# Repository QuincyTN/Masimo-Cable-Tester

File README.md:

# Masimo-Cable-Tester
This repository describes SD Cables sponsored project: “Automated multi conductor
cable break-short detector,” hereinafter referred to as the “Cable Tester.” The Cable Tester
continuously monitors a multi-conductor cable that is being subjected to destructive mechanical
testing, measuring resistance and detecting any breaks or shorts. The team is developing a
Printed Circuit Board (PCB) that will have serval inputs and outputs (I/O), including SD card
port, 20-pin connector, power switch, DC power jack, a debugger, banana jack, and a Human
Machine Interface (HMI). For the HMI, the team will be using a Liquid Crystal Display (LCD)
to display the Graphic User Interface (GUI), which is shown for use case. We will be using the
AVR128DB64 microcontroller (MCU) help to drive our device.

The Cable Tester is a device that must test and analyze the
durability and integrity of wires. The device must extract data from the wire connected to
characterize it and monitor the changes in the wire that may indicate ashort or a break in the
conductors while the wire is subjected to a destructive mechanical test, such as a bend cycle test.
All data must be captured in an SD card inserted into the device for post-test analysis. Currently,
the Cable Tester that Masimo possesses operates with preset assumptions about the wire it will
attach. The Cable Tester that we design must be universal to all wires, more specifically, it must
characterize the cable regardless of what wire is connected and then proceed with the tests. The
universalizability of the Cable Tester will assist Masimo, and potentially other companies, in the
development of electrical systems by predetermining faults in the wires before it will be
implemented into the system, which prevents future technical issues.

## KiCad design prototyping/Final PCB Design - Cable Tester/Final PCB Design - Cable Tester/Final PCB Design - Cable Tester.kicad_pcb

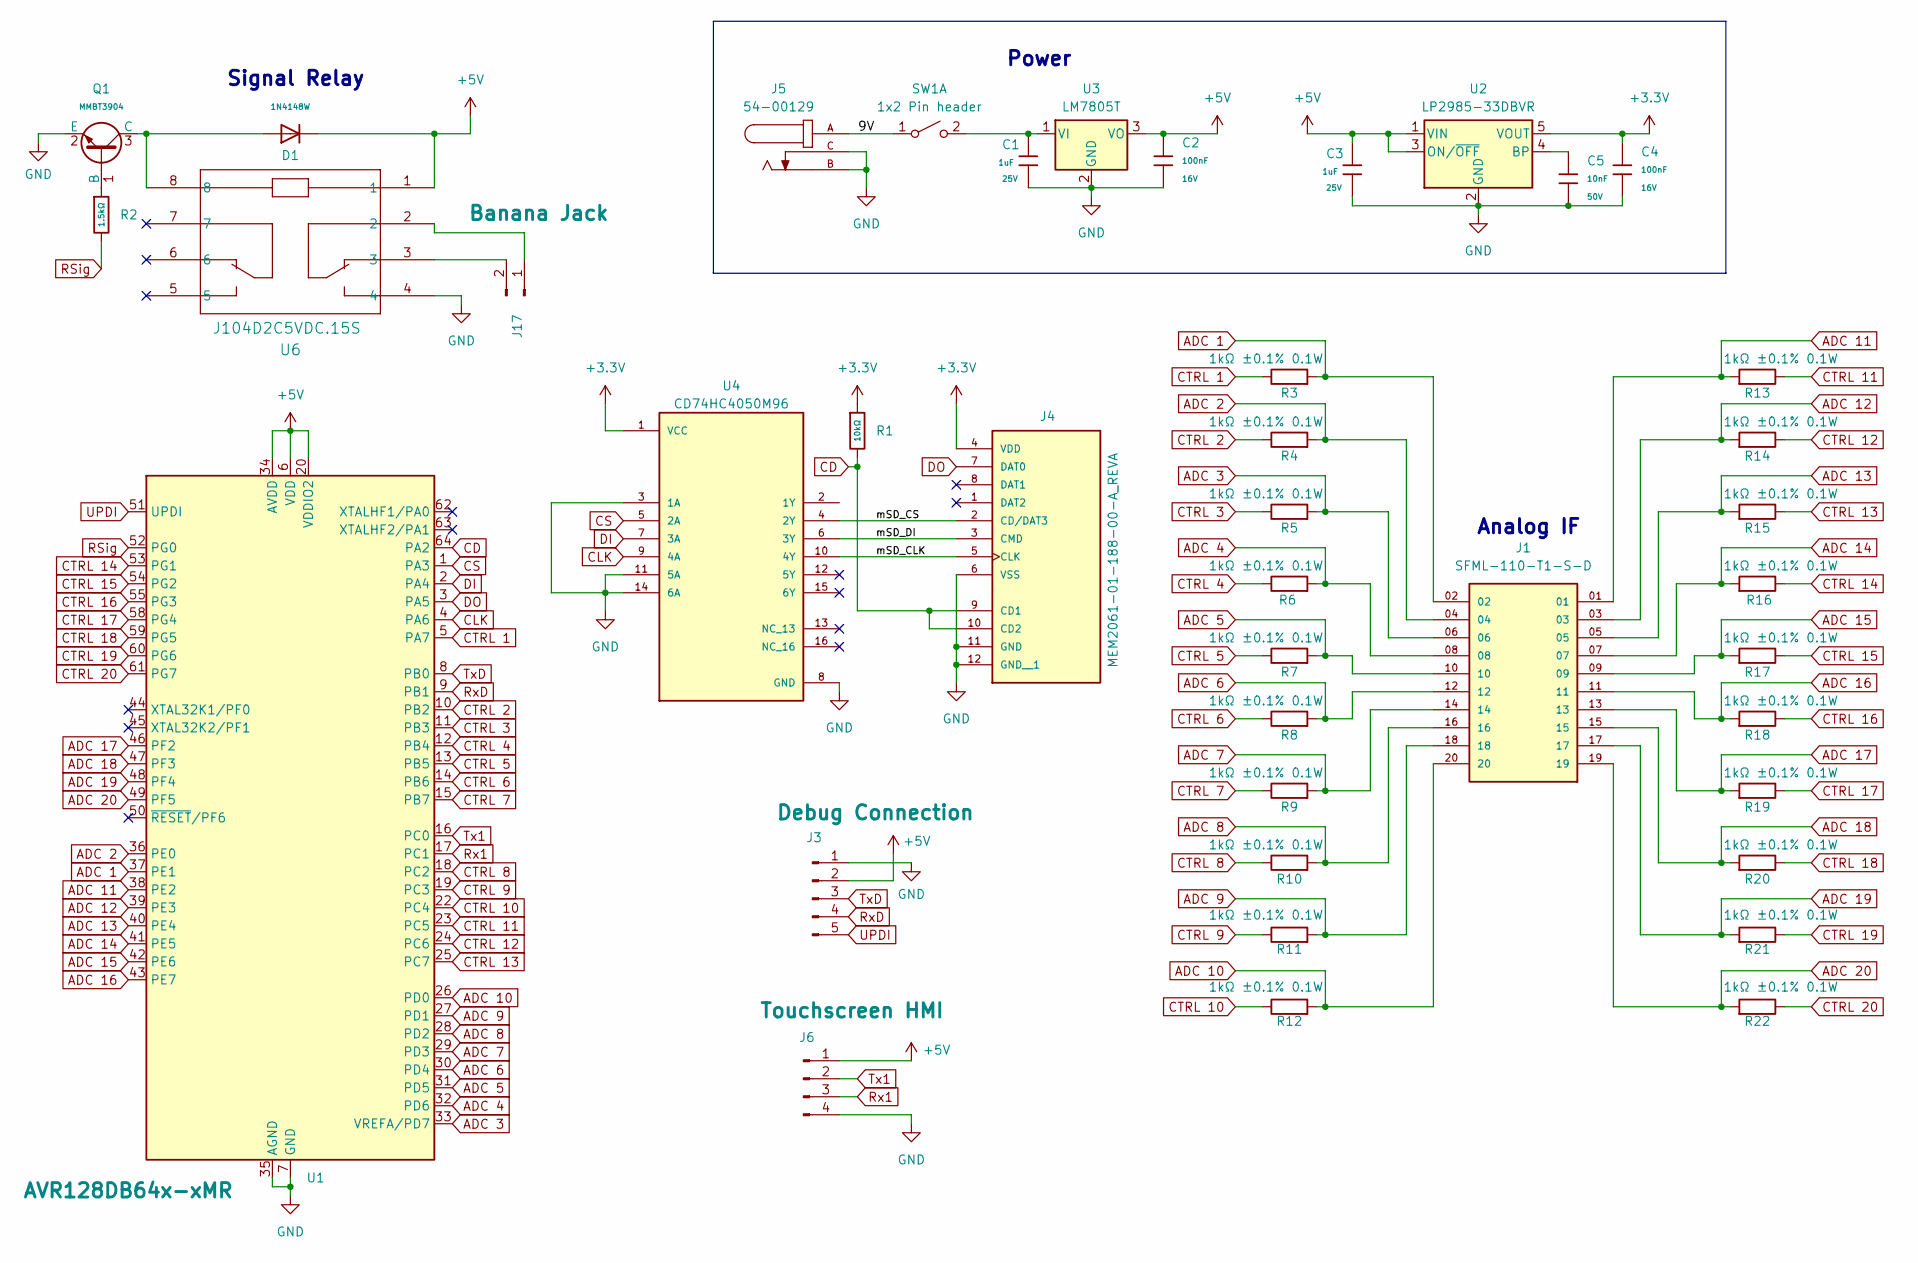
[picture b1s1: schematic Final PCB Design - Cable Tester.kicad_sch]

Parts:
C1, C3: 1uF; C_0402; Voltage Rated 25V; Tolerance ±10%; Part CL05A105KA5NQNC; LCSC C52923
C2, C4: 100nF; C_0402; Voltage Rated 16V; Tolerance ±10%; Part CL05B104KO5NNNC; LCSC C1525
C5: 10nF; C_0402; Voltage Rated 50V; Tolerance ±10%; Part CL05B103KB5NNNC; LCSC C15195
D1: 1N4148W; D_SOD-123; Forward Voltage (Vf@If) 1V@50mA; Reverse Voltage (Vr) 75V; Part 1N4148W; LCSC C81598
J1: SFML-110-T1-S-D; SAMTEC_SFML-110-T1-S-D; PARTREV E
J3: Debug Connection; PinHeader_1x05_P2.54mm_Vertical
J4: MEM2061-01-188-00-A_REVA; GCT_MEM2061-01-188-00-A_REVA
J5: 54-00129; TENSILITY_54-00129; PARTREV A
J6: Touchscreen HMI; PinHeader_1x04_P2.54mm_Vertical
J17: Banana Jack; PinHeader_1x02_P2.54mm_Vertical
Q1: MMBT3904; Q_SOT-23; Part MMBT3904; LCSC C7420353
R1: 10kΩ; R_1206; Overload Voltage (Max) 200V; Tolerance ±1%; Part 1206W4F1002T5E; LCSC C17902
R2: 1.5kΩ; R_0805; Overload Voltage (Max) 150V; Tolerance ±1%; Part 0805W8F1501T5E; LCSC C4310
R3, R4, R5, R6, R7, R8, R9, R10, R11, R12, R13, R14, R15, R16, R17, R18, R19, R20, R21, R22: 1kΩ ±0.1% 0.1W; R_0603
SW1: 1x2 Pin header; PinHeader_1x02_P2.54mm_Vertical
U1: AVR128DB64x-xMR; VQFN-64-1EP_9x9mm_P0.5mm_EP7.15x7.15mm
U2: LP2985-33DBVR; SOT-23-5
U3: LM7805T; TO-220-3_Vertical
U4: CD74HC4050M96; SOIC127P600X175-16N; PARTREV February 2005
U6: J104D2C5VDC.15S; RELAY8_J104D2C5VDC.20S_CRS

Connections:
+3.3V: C4.1, J4.4 (VDD), R1.1, U2.5 (VOUT), U4.1 (VCC)
+5V: C2.1, C3.1, D1.1, J3.2, J6.1, U1.6 (VDD), U1.20 (VDDIO2), U1.34 (AVDD), U1.56 (VDD), U2.1 (VIN), U2.3 (ON/~OFF), U3.3 (VO), U6.1
/9V: J5.A, SW1.1 (A)
/mSD_CLK: J4.5 (CLK), U4.10 (4Y)
/mSD_CS: J4.2 (CD/DAT3), U4.4 (2Y)
/mSD_DI: J4.3 (CMD), U4.6 (3Y)
ADC 1: J1.02, R3.2, U1.37 (PE1)
ADC 2: J1.04, R4.2, U1.36 (PE0)
ADC 3: J1.06, R5.2, U1.33 (VREFA/PD7)
ADC 4: J1.08, R6.2, U1.32 (PD6)
ADC 5: J1.10, R7.2, U1.31 (PD5)
ADC 6: J1.12, R8.2, U1.30 (PD4)
ADC 7: J1.14, R9.2, U1.29 (PD3)
ADC 8: J1.16, R10.2, U1.28 (PD2)
ADC 9: J1.18, R11.2, U1.27 (PD1)
ADC 10: J1.20, R12.2, U1.26 (PD0)
ADC 11: J1.01, R13.2, U1.38 (PE2)
ADC 12: J1.03, R14.2, U1.39 (PE3)
ADC 13: J1.05, R15.2, U1.40 (PE4)
ADC 14: J1.07, R16.2, U1.41 (PE5)
ADC 15: J1.09, R17.2, U1.42 (PE6)
ADC 16: J1.11, R18.2, U1.43 (PE7)
ADC 17: J1.13, R19.2, U1.46 (PF2)
ADC 18: J1.15, R20.2, U1.47 (PF3)
ADC 19: J1.17, R21.2, U1.48 (PF4)
ADC 20: J1.19, R22.2, U1.49 (PF5)
CD: J4.9 (CD1), J4.10 (CD2), R1.2, U1.64 (PA2)
CLK: U1.4 (PA6), U4.9 (4A)
CS: U1.1 (PA3), U4.5 (2A)
CTRL 1: R3.1, U1.5 (PA7)
CTRL 2: R4.1, U1.10 (PB2)
CTRL 3: R5.1, U1.11 (PB3)
CTRL 4: R6.1, U1.12 (PB4)
CTRL 5: R7.1, U1.13 (PB5)
CTRL 6: R8.1, U1.14 (PB6)
CTRL 7: R9.1, U1.15 (PB7)
CTRL 8: R10.1, U1.18 (PC2)
CTRL 9: R11.1, U1.19 (PC3)
CTRL 10: R12.1, U1.22 (PC4)
CTRL 11: R13.1, U1.23 (PC5)
CTRL 12: R14.1, U1.24 (PC6)
CTRL 13: R15.1, U1.25 (PC7)
CTRL 14: R16.1, U1.53 (PG1)
CTRL 15: R17.1, U1.54 (PG2)
CTRL 16: R18.1, U1.55 (PG3)
CTRL 17: R19.1, U1.58 (PG4)
CTRL 18: R20.1, U1.59 (PG5)
CTRL 19: R21.1, U1.60 (PG6)
CTRL 20: R22.1, U1.61 (PG7)
DI: U1.2 (PA4), U4.7 (3A)
DO: J4.7 (DAT0), U1.3 (PA5)
GND: C1.2, C2.2, C3.2, C4.2, C5.2, J3.1, J4.6 (VSS), J4.11 (GND), J4.12 (GND__1), J5.B, J5.C, J6.4, Q1.2 (E), U1.7 (GND), U1.21 (GND), U1.35 (AGND), U1.57 (GND), U1.65 (GND), U2.2 (GND), U3.2 (GND), U4.3 (1A), U4.8 (GND), U4.11 (5A), U4.14 (6A), U6.4
unnamed: J17.1, U6.2
unnamed: J17.2, U6.3
unnamed: Q1.1 (B), R2.1
unnamed: D1.2, Q1.3 (C), U6.8
unnamed: C1.1, SW1.2 (B), U3.1 (VI)
unnamed: C5.1, U2.4 (BP)
RSig: R2.2, U1.52 (PG0)
Rx1: J6.3, U1.17 (PC1)
RxD: J3.4, U1.9 (PB1)
Tx1: J6.2, U1.16 (PC0)
TxD: J3.3, U1.8 (PB0)
UPDI: J3.5, U1.51 (UPDI)

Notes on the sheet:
Power
Signal Relay
Analog IF

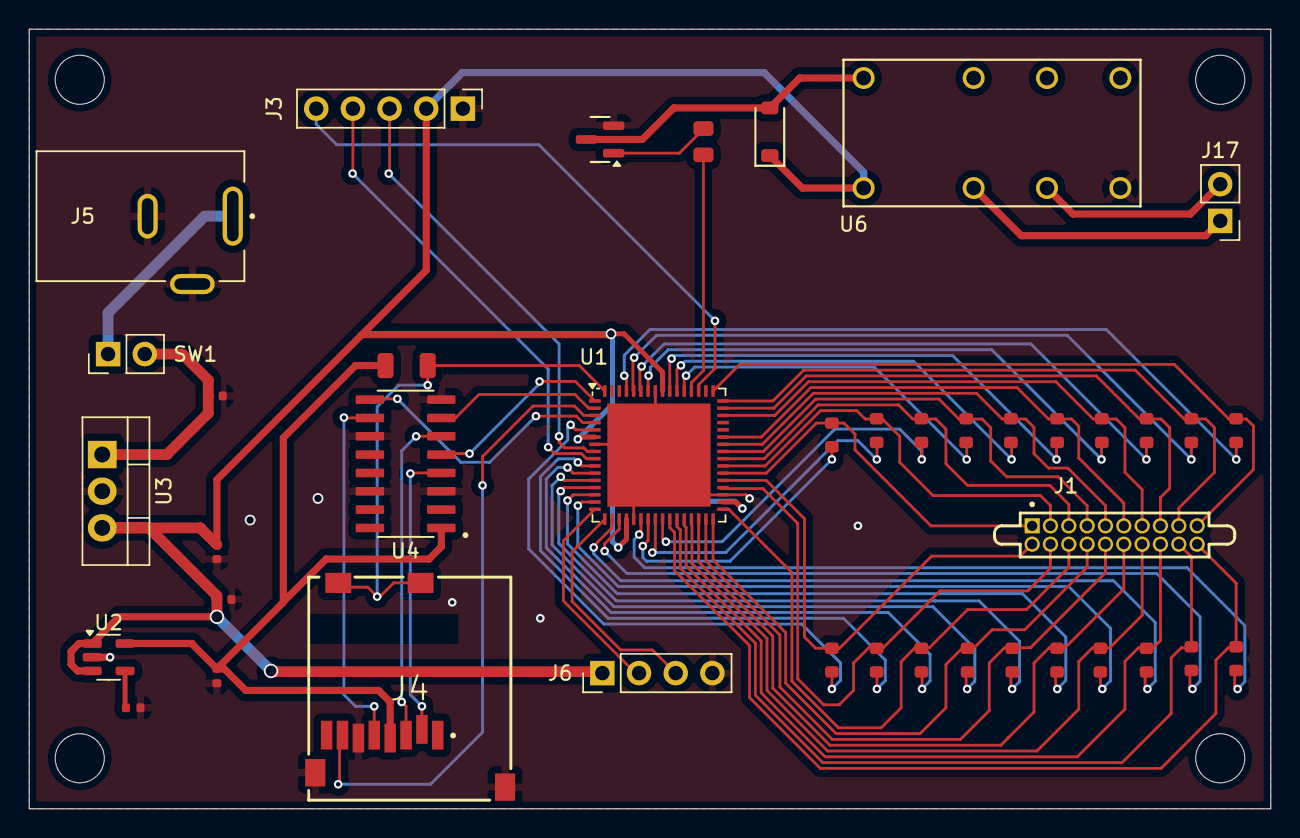
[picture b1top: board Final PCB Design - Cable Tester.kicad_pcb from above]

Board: 2 copper layers, 86.0 x 54.0 mm, 41 parts (0 on the bottom side), 64 nets.

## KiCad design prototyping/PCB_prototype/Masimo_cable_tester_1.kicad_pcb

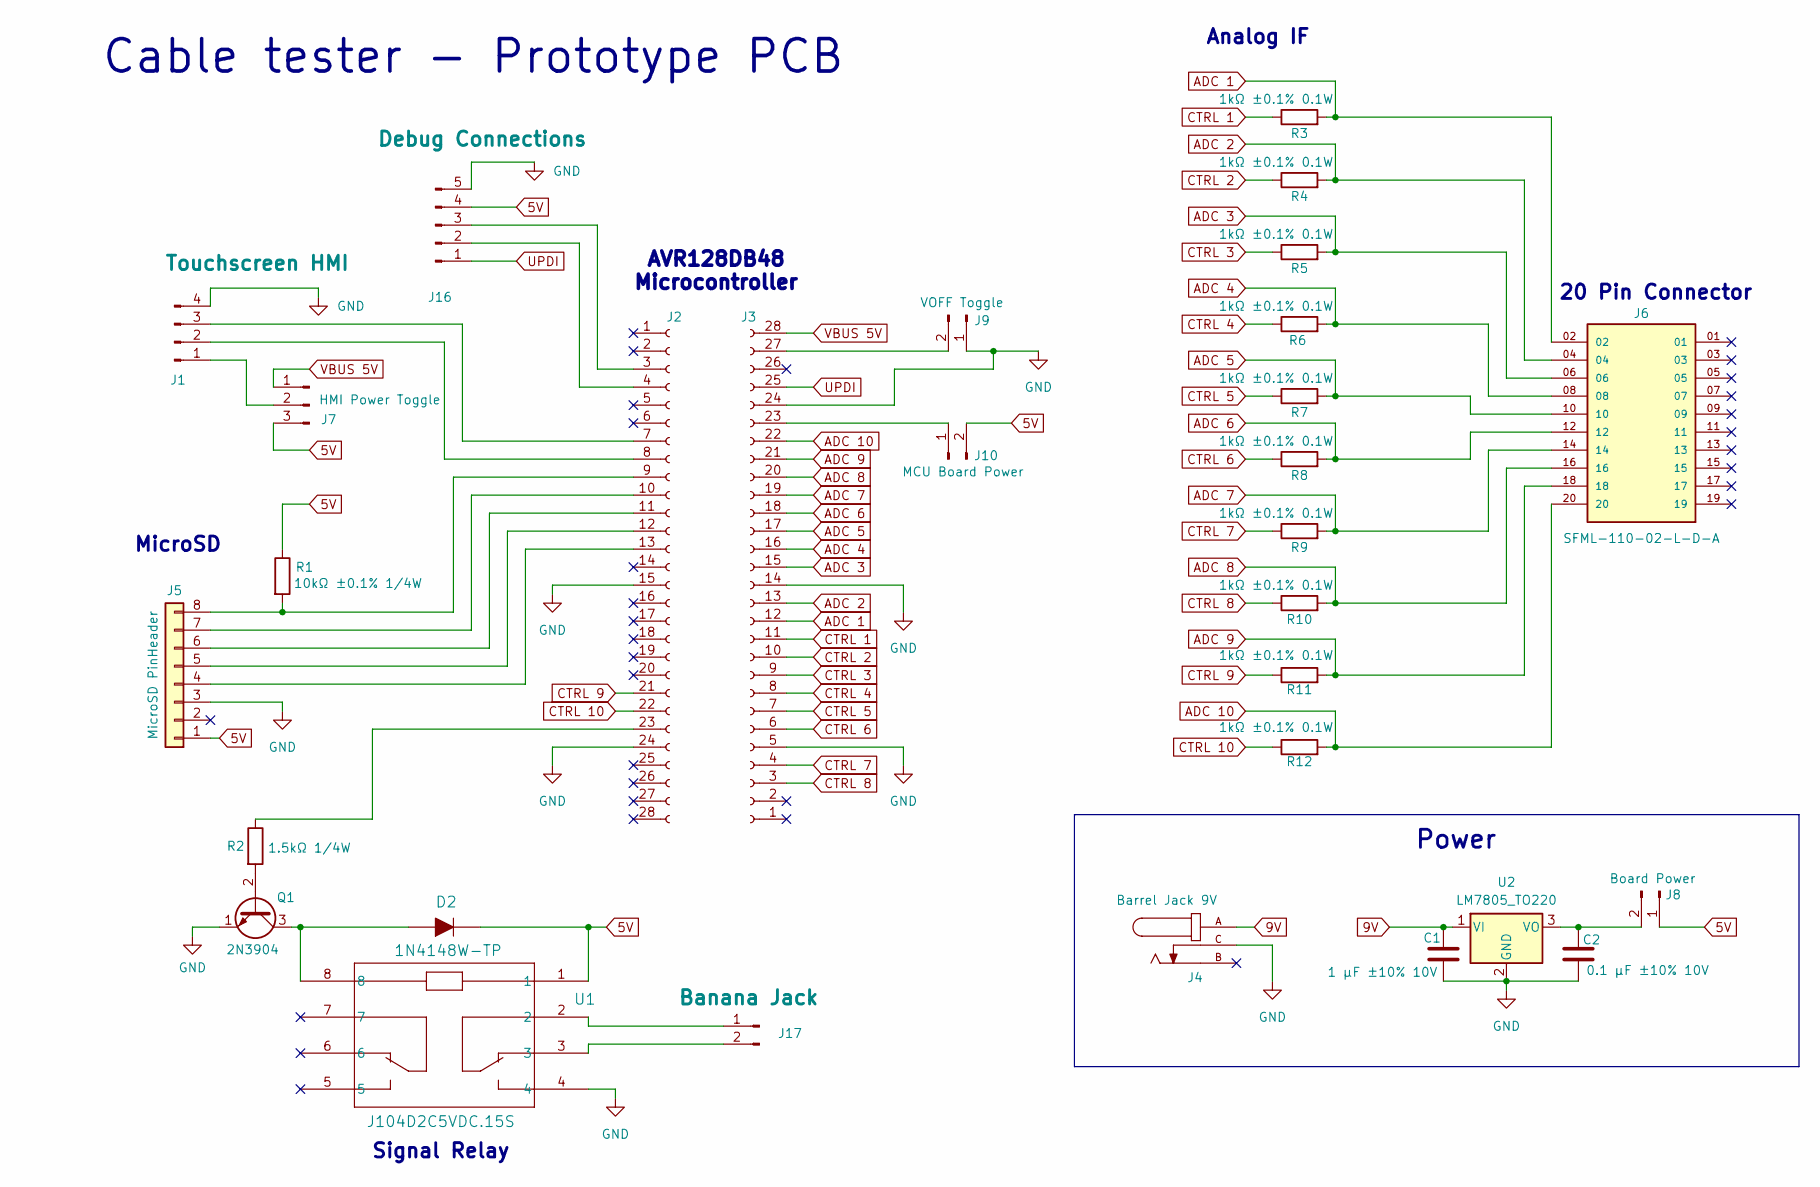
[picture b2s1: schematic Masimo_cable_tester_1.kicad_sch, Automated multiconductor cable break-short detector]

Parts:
C1: 1 µF ±10% 10V; CAP_CL10_SAM
C2: 0.1 µF ±10% 10V; CAP_CL05_SAM
D2: 1N4148W-TP; SOD-123; MPN 1N4148W-TP; Digi-Key_PN 1N4148WTPMSCT-ND
J1: Touchscreen HMI; PinHeader_1x04_P2.54mm_Vertical
J2: Curiosity Nano AVR128DB48; PinHeader_1x28_P2.54mm_Vertical
J3: Conn_01x28_Socket; PinHeader_1x28_P2.54mm_Vertical
J4: Barrel Jack 9V; TENSILITY_54-00129; PARTREV A
J5: MicroSD PinHeader; PinHeader_1x08_P2.54mm_Vertical
J6: SFML-110-02-L-D-A; SAMTEC_SFML-110-02-L-D-A; PARTREV E
J7: HMI Power Toggle; PinHeader_1x03_P2.54mm_Vertical
J8: Board Power; PinHeader_1x02_P2.54mm_Vertical
J9: VOFF Toggle; PinHeader_1x02_P2.54mm_Vertical
J10: MCU Board Power; PinHeader_1x02_P2.54mm_Vertical
J16: Debug Connections; PinHeader_1x05_P2.54mm_Vertical
J17: Banana Jack; PinHeader_1x02_P2.54mm_Vertical
Q1: 2N3904; TO-92_Inline
R1: 10kΩ ±0.1% 1/4W; RC0402N_PAN
R2: 1.5kΩ 1/4W; RES_ERA8AEB152V
R3, R4, R5, R6, R7, R8, R9, R10, R11, R12: 1kΩ ±0.1% 0.1W; RES_0816_SUS
U1: J104D2C5VDC.15S; RELAY8_J104D2C5VDC.20S_CRS
U2: LM7805_TO220; TO-220-3_Vertical

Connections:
5V: D2.K, J5.1, J7.3, J8.1, J10.2, J16.4, R1.1, U1.1
9V: C1.1, J4.A, U2.1 (VI)
ADC 1: J3.12, J6.02, R3.2
ADC 2: J3.13, J6.04, R4.2
ADC 3: J3.15, J6.06, R5.2
ADC 4: J3.16, J6.08, R6.2
ADC 5: J3.17, J6.10, R7.2
ADC 6: J3.18, J6.12, R8.2
ADC 7: J3.19, J6.14, R9.2
ADC 8: J3.20, J6.16, R10.2
ADC 9: J3.21, J6.18, R11.2
ADC 10: J3.22, J6.20, R12.2
CTRL 1: J3.11, R3.1
CTRL 2: J3.10, R4.1
CTRL 3: J3.9, R5.1
CTRL 4: J3.8, R6.1
CTRL 5: J3.7, R7.1
CTRL 6: J3.6, R8.1
CTRL 7: J3.4, R9.1
CTRL 8: J3.3, R10.1
CTRL 9: J2.21, R11.1
CTRL 10: J2.22, R12.1
GND: C1.2, C2.2, J1.4, J2.15, J2.24, J3.5, J3.14, J3.24, J4.C, J5.3, J9.1, J16.5, Q1.1 (E), U1.4, U2.2 (GND)
unnamed: J1.1, J7.2
unnamed: J1.2, J2.8
unnamed: J1.3, J2.7
unnamed: J2.9, J5.8, R1.2
unnamed: J2.10, J5.7
unnamed: J2.11, J5.6
unnamed: J2.12, J5.5
unnamed: J2.13, J5.4
unnamed: J2.23, R2.1
unnamed: J3.27, J9.2
unnamed: C2.1, J8.2, U2.3 (VO)
unnamed: J3.23, J10.1
unnamed: J2.4, J16.2
unnamed: J2.3, J16.3
unnamed: J17.1, U1.2
unnamed: J17.2, U1.3
unnamed: Q1.2 (B), R2.2
unnamed: D2.A, Q1.3 (C), U1.8
UPDI: J3.25, J16.1
VBUS 5V: J3.28, J7.1

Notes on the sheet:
Signal Relay
MicroSD
20 Pin Connector
Cable tester - Prototype PCB
Power
AVR128DB48 Microcontroller
Analog IF

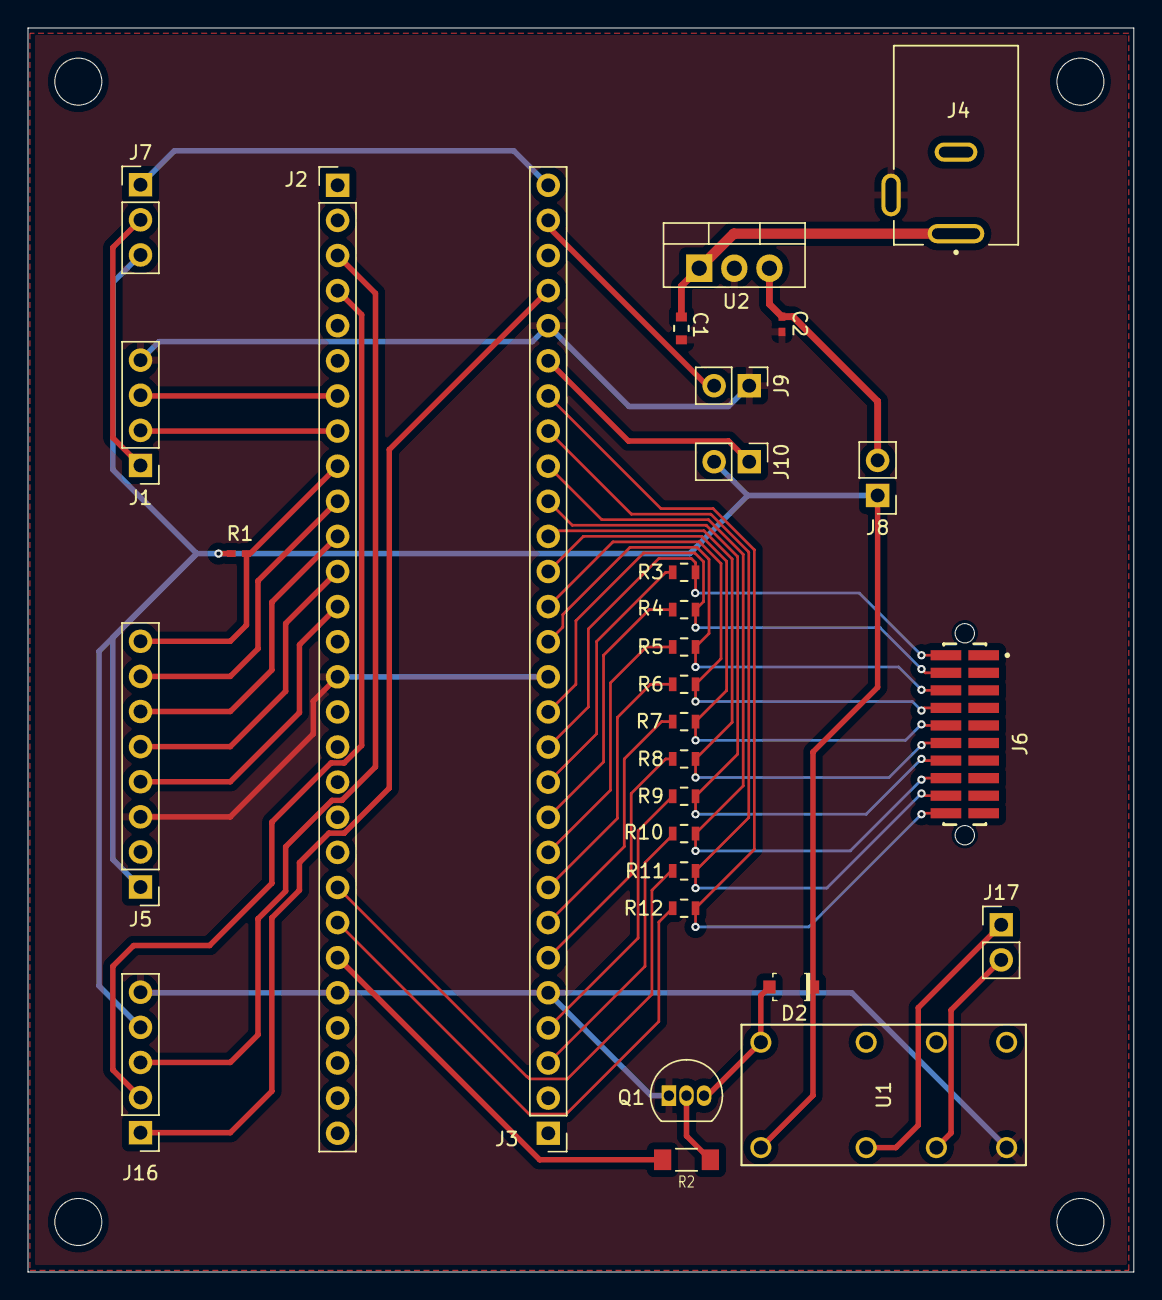
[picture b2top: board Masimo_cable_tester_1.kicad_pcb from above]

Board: 2 copper layers, 80.0 x 90.0 mm, 30 parts (0 on the bottom side), 43 nets.

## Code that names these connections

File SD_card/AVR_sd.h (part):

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
// Define the SPI pins for an AVR128DBxx
// *********************************
// #define CARD_CS_PORT		PORTE		// PE2
// #define CARD_CS_PIN			PIN2_bm		// 2
// #define CARD_DETECT_PORT	PORTE		// PE3 
// #define CARD_DETECT_PIN		PIN3_bm		// 3

#define CARD_CS_PORT		PORTA		// PA2
#define CARD_CS_PIN			PIN3_bm		// 2
#define CARD_DETECT_PORT	PORTA		// PA2
#define CARD_DETECT_PIN		PIN2_bm		// 2

#define CD_ISR_VECT			PORTE_PORT_vect // vector for card detect ISR
#define CD_INT_SENSE		0x02			// enable interrupt on either edge 
#define CD_PIN_CTRL			PIN3CTRL		// to enable interrupts on card insert/removal
#define SPI_MOSI_PORT		PORTA		// PA4
#define SPI_MOSI_PIN		PIN4_bm		// 4
#define SPI_MISO_PORT		PORTA		// PA5
#define SPI_MISO_PIN		PIN5_bm		// 5
#define SPI_SCK_PORT		PORTA		// PA6
#define SPI_SCK_PIN			PIN6_bm		// 6
#define SPI_SS_PORT			PORTA		// PA7 - disabled, using this pin PER_CLK output
#define SPI_SS_PIN			PIN7_bm		// 7

#define CARD_DETECT_SENSE	1	// set to 1 if card inserted asserts the CD line high,
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
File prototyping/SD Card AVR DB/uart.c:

/* ***********************************************************************
 * Simplified UART functions to support SD card usage
 * Author:  Glenn Pohly
 * Date:	6/1/2024 
 * this is a vastly simplified version of the UART functions distributed by Liviu Istrate
 * with his excellent SD Card utilities.  See "fat.c" for his contact info and info on 
 * the SD card utility and the public license.
 *  This software is freely distributed for use as you may see fit.
 */

#include <stdio.h>		
#include <avr/io.h>		// pin defs for the MCU
#include <avr/interrupt.h>

#include "uart.h"		// defines for the UART functions
#include "utils.h"		// string conversion functions


/* variable & constants */
char USART_ReceiveBuffer[RX_BUF_MAX+1];				// Global Buffer, add 1 for null character
char hex_data[MAX_HEX+3];							// max hex digits to convert to string + 3 for '0x" and NULL
bool new_data = false;								// flag set by RX ISR to tell system new data is available
													// must declare hex_data[] and new_data as EXTERN in main
const char hex_array[] = "0123456789ABCDEFx";		// used to convert hex numbers to a string


/* ******************************************************************************
   ********************  start of UART functions  *******************************
   ******************************************************************************/

//function to initialize UART
void uart_init (void)
{
	/*
	// USART1 on an AVR128DA48.  TX is pin PC0, RX PC1 
	// USART3 on an AVR128DB48.  TX is pin PB0, RX is PB1
	// USART2 on an AVR128DB48 Curiosity Nano needs to be moved to an alternate pin config
	DB_USART.BAUD = BAUD_PRESCALE;				// set baud rate
	DB_USART.CTRLC |= USART_CHSIZE_8BIT_gc;		// 8bit data format
	DB_PORT.DIR	 |= TX_PIN;						// set TX pin as output
	DB_USART.CTRLB |= USART_TXEN_bm;			// enable transmitter
	DB_USART.CTRLA |= USART_RXCIE_bm;			// enable receiver interrupt
	DB_USART.CTRLB |= USART_RXEN_bm;			// enable receiver
	sei();										// enable global interrupts
	*/
	uint16_t B = 64UL * F_CPU / (16UL * 9600);	//calculate aysynchronous baudrate
	PORTMUX.USARTROUTEA &= 0;	//USART3 using PB0 as TxD and PB1 as RxD
	PORTB.DIRSET = (1 << 0);    //Set PB0 as output (TxD)
	PORTB.DIRCLR = (1 << 1);	//Set PB1 as input (RxD)

	USART3.BAUD = B;
	
	//USART3.CTRLC |= (1<<6);		//USART is synchronous, no parity bit, 1 stop bit, 8 char data size
	USART3.CTRLB = (USART_RXEN_bm) | (USART_TXEN_bm); //enable receiver and transmitter
	
	USART3.CTRLA = (USART_RXCIE_bm);	//enable receive complete interrupt
}

/*  Function to receive a character from UART */
char uart_receive ()
{
	while ( !( DB_USART.STATUS & USART_RXCIF_bm) );		// wait for data in the receive buffer
	return DB_USART.RXDATAL;							// return received data
}

// RX ISR to receive a line of data
ISR(DB_USART_RXC_vect)
{
	uint8_t i = 0;
	char new_char;
	
	// can only get here if a char was received in the RX buffer
	do{
		new_char = uart_receive();
		USART_ReceiveBuffer[i++] = new_char;
	  }  while(new_char != '\r' && i < RX_BUF_MAX);
	USART_ReceiveBuffer[--i] = '\0';			// replace \r with null
	// if(i == RX_BUF_MAX)
	//	USART_ReceiveBuffer[--i] = '\r';		// received data too long for buffer, force a newline
	DB_USART.CTRLB &= ~USART_RXEN_bm;				// disable receiver (prevents buffer overrun)
	DB_USART.CTRLA &= ~USART_RXCIE_bm;			// disable receiver interrupt
	DB_USART.RXDATAL = 0;                         // clear RX data register in case of overrun
	// no new data can be received until buffer is read and RX and RX INT are re-enabled.
	
	new_data = true;							// Tell system data is available
}


/*  Function to send one char of a string char out UART  */
void uart_transmit (char data) {
	while (!( DB_USART.STATUS & USART_DREIF_bm));     // busy loop; until register is free
	DB_USART.TXDATAL = data;							// load data in the register
}

/* Function to transmit a string of data.  String MUST end in a NULL  */
void uart_send(char data[]){
	int i = 0;
	do {
		uart_transmit(data[i]);
	} while(data[i++] != '\0');
}

/* Function to transmit a string of data.  String MUST end in a NULL  */
void UART_sendString(char s[]){
	int i = 0;
	do {
		uart_transmit(s[i]);
	} while(s[i++] != '\0');
}

/* Function to transmit a string of data.  String MUST end in a NULL.  Adds a newline char at end  */
void UART_sendStringn(char s[]){
	int i = 0;
	do {
		uart_transmit(s[i]);
	} while(s[i++] != '\0');
	uart_transmit('\n');
}

/* function to re-enable RX after a received buffer has been read  */
void enable_rx1(void) {
	/* prepare the receive buffer to get more data. 
	* **** DO NOT RE-ENABLE RX *** until you have saved the recieved data if needed!
	* re-enabling will allow the RX to immediately over-write the receive data buffer. */
	new_data = false;	// clear new data flag
	DB_USART.CTRLA |= USART_RXCIE_bm;			// enable receiver interrupt
	DB_USART.CTRLB |= USART_RXEN_bm;			// enable receiver
} 
				
/* function to format an 8-bit number into ASCII hex format string and send */
void UART_sendHex8(uint8_t hex_num){
	uint8_t temp_num;
	
	hex_data[0] = hex_array[0];
	hex_data[1] = hex_array[16];
	temp_num = hex_num >> 4;
	hex_data[2] = hex_array[temp_num];
	temp_num = hex_num & 0x0F;
	hex_data[3] = hex_array[temp_num];
	hex_data[4] = '\0';
	UART_sendString(hex_data);
}

/* function to format a 16-bit number into ASCII hex format string and send */
void UART_sendHex16(uint16_t hex_num){
	uint16_t temp_num;
	
	hex_data[0] = hex_array[0];
	hex_data[1] = hex_array[16];
	temp_num = hex_num >> 12;
	hex_data[2] = hex_array[temp_num];
	temp_num = hex_num >> 8 & 0x000F;
	hex_data[3] = hex_array[temp_num];
	temp_num = hex_num >> 4 & 0x000F;
	hex_data[4] = hex_array[temp_num];
	temp_num = hex_num & 0x0F;
	hex_data[5] = hex_array[temp_num];
	hex_data[6] = '\0';
	UART_sendString(hex_data);
}


void STRING_hextoa(uint16_t hex_num, char s[]){
	// assumes an int size hex num.
	uint16_t	temp_num;
	
	s[0] = hex_array[0];
	s[1] = hex_array[16];
	temp_num = hex_num >> 12;
	s[2] = hex_array[temp_num];
	temp_num = hex_num >> 8 & 0x000F;
	s[3] = hex_array[temp_num];
	temp_num = hex_num >> 4 & 0x000F;
	s[4] = hex_array[temp_num];
	temp_num = hex_num & 0x000F; 
	s[5] = hex_array[temp_num];
	s[6] = '\0';
	}  // end STRING_hextoa

void UART_sendInt(INT_SIZE number){
	char string[MAX_NR_OF_DIGITS + 1] = {0};
	
	STRING_itoa(number, string, 0);
	UART_sendString(string);
}

/* ********************  end of UART functions  ********************************* */

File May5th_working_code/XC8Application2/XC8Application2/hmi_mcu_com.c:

#include "hmi_mcu_com.h"

void initUSART1(){
	//Initialize USART1 in ASynchronous mode with baudrate 9600
		
	uint16_t BAUDRATE = 64UL * F_CPU / (16UL * BAUDr);	//calculate aysynchronous baudrate
	//PORTMUX.USARTROUTEA = PORTMUX_USART2_ALT1_gc;	//USART2 using PF4 as TxD and PF5 as RxD
	PORTMUX.USARTROUTEA = PORTMUX_USART1_DEFAULT_gc;
	
	PORTC.DIRSET = PIN0_bm;		//SET PC0 as output (Tx1)
	PORTC.DIRCLR = PIN1_bm;		//set PC1 as input (Rx1)

	USART1.BAUD = BAUDRATE;

	USART1.CTRLB = (USART_RXEN_bm) | (USART_TXEN_bm);	//enable receiver and transmitter

	USART1.CTRLA = (USART_RXCIE_bm);	//enable receive complete interrupt
}
void transmitHmi(char* page, char* ID, char* field, char* value, uint8_t action){
	/*
	This function will send commands to the HMI. page
	*/
	char command[BUFFER_SIZE*3];
	int len = 0;
	
	if(action == 1){//if the MCU needs a value from HMI (request is 1)
		len = sprintf(command, "get %s.%s.%s%c%c%c", page, ID, field, 0xFF, 0xFF, 0xFF);
	}
	else if(action == 2){//if the MCU update text box in HMI
		len = sprintf(command, "%s.%s.txt=\"%s\"%c%c%c", page, ID, value, 0xFF, 0xFF, 0xFF);
	}
	else if(action == 3){ //if the MCU update number value in HMI
		int my_int = atoi(value);
		len = sprintf(command, "%s.%s.val=%d%c%c%c", page, ID, my_int, 0xFF, 0xFF, 0xFF);
	}
	else if(action == 4){//if the MCU needs to go to another page
		len = sprintf(command, "page %s%c%c%c", page, 0xFF, 0xFF, 0xFF);
	}
	else if(action == 5){//if the MCU needs a value from a HMI variable
		len = sprintf(command, "get %s%c%c%c", ID, 0xFF, 0xFF, 0xFF);
	}
	
	for(int i = 0; i < len; i++){
		while(!(USART1.STATUS & (USART_DREIF_bm)));	//wait until all data in buffer is sent
		USART1.TXDATAL = (char)command[i];	//send new char
	}
}
char* parseHmiString(char* string){
	//Return a string in the format of STRING_MESSAGE
	int dataLength = strlen(string);
	char* parsedStr = (char*)malloc(dataLength - 3);
	strncpy(parsedStr, string+1, dataLength+1);
	parsedStr[dataLength-4] = '\0';
	
	return parsedStr;	
}
uint32_t parseHmiInt(char* string){
	//Return a 32 integer number in the format of NUM_MESSAGE
	return ((uint32_t)string[1]) | ((uint32_t)string[2]<<8) | ((uint32_t)string[3]<<16) | ((uint32_t)string[4]<<24);
}
void parseHmiData(char* strData){

	if(strData[0] == STRING_MESSAGE){
		//char string[dataLength];
		//strncpy(string, strData+1, dataLength+1);
		//string[dataLength-4] = "\0";

		//transmitTerminal(parseHmiString(strData));
	}
	else if(strData[0] == NUM_MESSAGE){
		char number[BUFFER_SIZE];
		uint32_t intValue = parseHmiInt(strData);

		sprintf(number, "%lu", intValue);	//convert the integer to a string of characters
	}
	else if(strData[0] == START_CHAR){
		
		newCharacterization = 1;	
	}
	else if(strData[0] == START_TEST){
		// Set flags and timers to low and 0
		newCharacterization = 0;
		testingPause = 0;
		lastSdWrite = 0;
		faultDetected = 0;
		totalNumFaults = 0;
		
		char temp[100];
		sprintf(temp, "%0.2lu/%0.2lu/%0.4lu %0.2lu:%0.2lu:%0.2lu", month, day, year, hour, minute, second);
		transmitHmi(PAGE_TESTING, START_TIME_TXT, NULL, temp, 2);
		
		sprintf(temp, "%lu", totalNumFaults);
		transmitHmi(PAGE_TESTING, NUM_FAULTS, NULL, temp, 2);	//update total number of faults
		
		testingStart = 1;
		
	}
	else if(strData[0] == STOP_TEST){
		testingStart = 0;
		testingPause = 0;
		lastSdWrite = 0;	// reset last written values
		faultDetected = 0;	// reset flag, no fault is detected
		
		PORTG.OUTSET = PIN0_bm;	// reset relay to open
	}
	else if(strData[0] == PAUSE_TEST){
		//testingStart = 1;
		testingPause = 1;
	}
	else if(strData[0] == UNPAUSE_TEST){
		testingPause = 0;
	}
	else if(strData[0] == UPDATE_RATE){
		rate = parseHmiInt(strData);
		convertRate(); //update the rate in seconds
	}
	else if(strData[0] == UPDATE_RATE_UNIT){
		strcpy(rate_unit, parseHmiString(strData));
		convertRate(); //update the rate in seconds
	}
	else if(strData[0] == UPDATE_MODE){
		// 0 = Normal mode
		// 1 = Bypass mode
		bypassMode = parseHmiInt(strData);
	}
	
	//memset(hmiBuffer, 0, sizeof(hmiBuffer));	//clear the hmiBuffer
}

void getTime(){
	// update local MCU time with RTC from HMI
	for(int i = 0; i < 6; i++){
		
		char rtcID[BUFFER_SIZE]; 
		newHmiMessage = 0;
		sprintf(rtcID, "rtc%d", i);	
		transmitHmi(NULL, rtcID, NULL, NULL, 5);	//request rtc values from HMI
		
		while (!newHmiMessage);  // wait until flag is set by ISR

		if(hmiBuffer[0] == NUM_MESSAGE){
			uint32_t val = parseHmiInt(hmiBuffer);  // get value from buffer

			switch(i){
				case 0: year = val; break;
				case 1: month = val; break;
				case 2: day = val; break;
				case 3: hour = val; break;
				case 4: minute = val; break;
				case 5: second = val; break;
				default: break;
			}
		}
		newHmiMessage = 0;
	}
}

void convertRate(){
	// Convert rate and rate units into total number of seconds (minimum of 1 second)
	
	if(strcmp(rate_unit, "/min") == 0){
		updateRateInS = (uint32_t)ceil(60.0f / rate);	
	}
	else{
		updateRateInS = (uint32_t)ceil(3600.0f / rate);
	}
	
	if(updateRateInS < 5)
		updateRateInS = 5;
}

void initTimer1s() {
	//Set the period for 1 second
	TCA0.SINGLE.PER = (F_CPU / PRESCALER) - 1; // 23437 for 1s

	//Enable overflow interrupt
	TCA0.SINGLE.INTCTRL = TCA_SINGLE_OVF_bm;

	//Set prescaler to 1024 and enable timer
	TCA0.SINGLE.CTRLA = TCA_SINGLE_CLKSEL_DIV1024_gc | TCA_SINGLE_ENABLE_bm;
}

ISR(USART1_RXC_vect){
	/*
	Interrupt occurs when HMI receives data (a command or action) from USART1 receiver
	*/
	
	uint8_t data = USART1.RXDATAL;

	//Check for start identifiers (0x70 or 0x71)
	if ((data != NULL) && !hmiReceiving) {
		dataIndexRx = 0;   //Reset index
		hmiReceiving = 1;      //Start recording message
		memset(receiveData, 0, sizeof(receiveData));	//clear buffer before new message
	}

	if (hmiReceiving) {
		receiveData[dataIndexRx++] = data;
		if (dataIndexRx >= 3 &&
		receiveData[dataIndexRx - 1] == 0xFF &&
		receiveData[dataIndexRx - 2] == 0xFF &&
		receiveData[dataIndexRx - 3] == 0xFF) {
			
			USART1.CTRLB &= ~USART_RXEN_bm;	//turn off the receiver
			USART1.CTRLA &= ~USART_RXCIE_bm;	//turn off the receive interrupt
			
			memset(hmiBuffer, 0, sizeof(hmiBuffer));	//reset buffer
			strcpy(hmiBuffer, receiveData);			//copy data into buffer
			
			hmiReceiving = 0;  //Stop receiving
			dataIndexRx = 0;  //Reset buffer index
			newHmiMessage = 1;	//set flag in main

			USART1.CTRLB |= USART_RXEN_bm;	//turn on the receiver
			USART1.CTRLA |= USART_RXCIE_bm;	//turn on the receive interrupt
		}
		
		//Prevent buffer overflow
		if (dataIndexRx >= BUFFER_SIZE) {
			dataIndexRx = 0;
			hmiReceiving = 0;
			newHmiMessage = 1;
		}
	}
}

ISR(TCA0_OVF_vect) {
	// Update time
	//Leap year logic
	if ((year % 4 == 0 && year % 100 != 0) || (year % 400 == 0))
		daysInMonth[2] = 29;
	else
		daysInMonth[2] = 28;
	
	second++;	//increment seconds
	
	if(second >= 60){
		minute++;
		second = 0;
	}
	if(minute >= 60){
		hour++;
		minute = 0;
	}
	if(hour >= 24){
		day++;
		hour = 0;
	}
	if(day >= daysInMonth[month]){
		month++;
		day = 1;
	}
	if(month >= 12){
		year++;
		month = 1;
	}
	
	// Sync time with HMI RTC every 15 minutes
	lastTimeUpdate++;
	if (lastTimeUpdate >= 900) {
		getTime();
		lastTimeUpdate = 0;
	}
	
	if(testingStart && !testingPause && !bypassMode)
		lastSdWrite++;
	
	if(lastSdWrite >= updateRateInS-1){
		//write testing values into sd card		
		SD_testing(fileNum);
		testNumber++;
		lastSdWrite = 0;
	}
	
	
	TCA0.SINGLE.INTFLAGS = TCA_SINGLE_OVF_bm;	//reset overflow flag
}

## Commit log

2024-10-14 add system description document
    The System Description document describes major details of how the device operates, what it is capable of, and the different components used to build it
2024-10-14 Create README.md
    READ.md describes the project and how it will be used
2024-10-14 add board layout image
    image of how the PCB of the device will be structured. This is the first iteration as the design may change
2024-10-18 testing discording webhook
    send a notification in discord that someone pushed in
2024-10-18 add rough PCB layout
    PCB layout of the Cable Tester. The SD card reader will need a level shifter in the future
2024-10-18 create GUI.HMI file
    this file will be used for prototyping with the GUI and HMI.
2024-10-22 blinking LED on MCU
    Create a blinking LED on MCU with 2s period. PORTx.DIRSET is used to set the pin direction. PORTx.OUT is used to set the output pin value. Purpose is to familiarize with the AVR128DB48 pins
2024-10-26 create test for HMI
    testing buttons and uploading code to HMI.
2024-10-31 create MCU_GUI_com
    begin prototyping MCU and GUI communication using USART. Learned how to set up USART. Next, complete transmit() and ISR for transmit. Test to see if MCU can send to HMI
2024-11-01 attempt to send data to HMI
    set up HMI screen (Just a text box). In microchip studio, try to set up USART. there should be a counter displayed on the HMI, but nothing is being sent. some problems may be the incorrect (overflow 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
2024-11-07 implement USART with interrupts
    interrupt will start after the transmit() function
2024-11-15 Attempt send data from HMI to MCU
    It does not work. The receive buffer does not fill up? Tried to implement receiver without the interrupt using receiver3() which reads 1 char. After pressing the HMI button, it does not read.
2024-11-18 try moving HMI to USART2
    cannot receive data from the ISR.
2024-11-19 finish USART transmitter and receiver
    HMI can receive and send data. Discard the transmitter ISR, and do all the transmission inside the transmitX() function. On boot up, the transmitter/receiver doesn't work, but functions normally afte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
2024-11-23 Upload Version 1 Schematic
2025-02-05 MCU processing 0x70 and 0x71 messages
    Process HMI return messages of numbers (0x70) and strings (0x71). Create da testing GUI to send these messages.
2025-02-05 Test the get command from the MCU to the HMI
    get number and text values from the HMI and display them on the terminal. Set up a timer and interrupt, which every 1 second will get values from the HMI.
2025-02-06 Updated the Prototyping PCB schematic
    Changed the signal relay symbol and footprint to the correct one. Added a flyback diode to the relay. Added the power required for each resistor. And various general updates to tags and connections.
2025-02-06 Files for the Relay
    I added the files for the KiCad symbol and footprint for the signal relay
2025-02-06 Begin HMI design
    Set up the startup page, outline the pages that the HMI will need
2025-02-06 Attaching footprints to MCU connector and SD card reader
2025-02-06 Added jumpers
2025-02-11 Debug Terminal Setup
    A Putty terminal can be used to take an input and do something on the MCU. Added parseTerminalData() and parseHmiData() functions to do an action after a new terminal or HMI message is received
2025-02-14 Fixing Error and More
    Fixed error where string would not display correctly on terminal. Also, information displayed on terminal was made nicer for viewing purposes. Worked on these things with Quincy.
2025-02-16 Fix Terminal Bug
    Fixed bug where terminal input disabled transmitTerminal(). Added addition functions to test
2025-02-18 Prototype schematic updates
2025-02-18 Added resistors footprint.
2025-02-18 Prototype board updates
    Added new components with footprints
2025-02-18 Added capacitor footprints.
2025-02-21 Prototype PCB updates and additions
    Consolidated the KiCad symbols and footprints used into a single folder to be used. Updated jumper footprints and started to organize the PCB components. (no traces yet).
2025-02-24 SD/MCU/GUI communication
    Successfully able to change a checkbox from true to false or vice versa based on if the SD card is inserted or not
2025-02-25 Sending integers to HMI
    Added a line that allows MCU to send an integer to the HMI.
    Purpose: Change the state of a checkbox
2025-02-25 Prototype Schematic and PCB Updates
    Made a few changes to the schematic for ease of tracing on the PCB design. Started PCB layout of components, no traces yet
2025-02-25 Add files via upload
    Characterization page
2025-02-27 Move terminal and HMI functions into header files
    Directories "Headers" and "Sources" declare and define those functions. "global_consts_vars" declares global constants and variables like buffers and flags that are used in the other header files. Be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
2025-02-27 testing stuff
    testing sd card capacity
2025-03-04 Updated Prototype PCB Layout
    Updated the prototype PCB layout. Tried optimizing placement of components for easier traces. Added an edge cut layer to made PCB 70mmx80mm
2025-03-04 Add the Final PCB design
    Added the final PCB design KiCad Folder
2025-03-05 Layed traces down.
2025-03-05 Update traces.
2025-03-05 Finish Settings page, create additional GUI pages
    Added Settings page to change data recording rate, rate unit, and mode.
    Added message codes (0x34, 0x35, 0x36) and the responses in parseHmiData().
    Create parseHmiString and parseHmiInt for easier data parsing.
    Added terminal command "settings" to display current test settings.
    TODO:
    - Implement "Start Test" button logic
2025-03-05 Prototype Schematic and PCB Update
    Updated the prototype schematic and PCB. Put all analog if tags on 1 side for easier PCB tracing. By doing this I also changed the location of the Rsig, CD, and CS locations on the MC.
2025-03-05 Prototype PCB Changes
    A few routing changes to the Prototype PCB.
2025-03-06 Testing
2025-03-06 Revert "Test push."
    This reverts commit 5521fc2d8bd7614dad4a2481f5d65b20cf141a6d, reversing
    changes made to 7098e4d101a90ac0b58b20fb139d108fe580d24d.
2025-03-06 PDB Update
2025-03-06 PCB Update
2025-03-06 Transfer PCB to new folder.
2025-03-06 Updated PCB.
2025-03-06 Updated power traces.
2025-03-06 Update PCB.
2025-03-06 Update debug terminal commands
    Also put more indicators for each command and if they succeeded
2025-03-06 Fixed errors and added labels to components.
2025-03-07 Updated Prototype Schematic and PCB
2025-03-07 Add more terminal commands
    more testing of the GUI and functions
2025-03-08 Final PCB Schematic updates
    updated the pinout for the 64pin MCU, added the FT232RL for rs232 translation, added a micro USB to be the debug connection, added a single pin for UPDI connection.
2025-03-10 Made traces thicker (0.4 mm).
2025-03-13 Final PCB schematic update
2025-03-17 Final PCB Schematic and PCB layout update
2025-03-20 Added ground plane.
2025-03-23 Prototype PCB update
    extended the board to add screw mount holes
2025-03-24 Changed spacing.
2025-03-24 Update.
2025-03-24 Changed spacing to account for overhang.
2025-03-25 Downloading files to order PCB.
2025-03-25 Added THT Prototype PCB
    Added the through hole prototype PCB board and schematics. Also added the symbols and footprints for THT PCB
2025-03-25 Laying out final PCB.
2025-03-27 Updated.
2025-03-28 Updated THT Prototype PCB
    Updates to the through hole prototype PCB design
2025-03-28 Updates to final PCB
    Final PCB design updates - placed traces and vias to Analog IF circuit and changed order of analog pins 1-10 on schematic and PCB layout.
2025-03-28 Updated Final PCB Layout
    Refined some of the ADC trace layouts. Less sharp corners and smoother traces
2025-03-28 updated prototype PCB layout
    Fixed backwards barrel jack and made small minor changes to silkscreen layer so that paint is not overlapping solder points.
2025-04-08 Update - Final PCB design
    Added more traces, added and fixed 3D footprints, other minor fixes
2025-04-08 Updated - Final PCB
    Added GND fill, places the rest of the trace lines, minor line adjustments.
2025-04-08 Updated Final PCB
    Minor fixes and changes. Moved some traces to not overlap from top and bottom traces
2025-04-10 Update - Final PCB to JLCPCB components
    Added the JLCPCB Library and updated to equivalent components supplied by JLCPCB. Also updated the PCB traces to fit new components.
2025-04-10 Updated - Final PCB - Fixed DRC issues
    Fixed all errors, warnings, or issues in the DRC checker for the final PCB
2025-04-10 Update - Final PCB
    Changed the Samtec connector and made minor adjustments
2025-04-10 Extracted files to order board.
2025-04-25 Changes to Final board design
    Re-routed the DO from microSD to MCU (No more level shifter), added a 5V line to pin 20 so that port C will be powered. Fixed other minor issues after running DRC on layout design.
2025-04-25 Updated final PCB
    Tied pin 3 of U4 to GND. Updated the Gerber files for manufacturing.
2025-04-25 zip file for testing 20-pin connector
    zip file for testing 20-pin connector on PCB
2025-04-28 Add files via upload
    Updated version for 20 control pins and 20 adc pins
2025-04-30 for ryan
    code for ADC stuff
2025-05-01 Add files via upload
    >:(
2025-05-03 Change HMI for AVR128DB64
2025-05-05 testing code
2025-05-05 Update for avr128db64
2025-05-05 20 pins working but not reading values
2025-05-05 This code works perfectly
2025-05-06 Latest working code
2025-05-06 Implement fault detection
2025-05-06 WIP fault detection
2025-05-06 doing a test after a test is broken
2025-05-06 WORKING fault detection
2025-05-07 Working for senior design day
    IT WORKS!!!!!!!
2025-05-07 Final fixes, everything is working
    clean up the code and comments

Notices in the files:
SD_card/AVR_sd.h:
----------------------------- LICENSE - GNU GPL v3 -----------------------------------------------
Copyright (C) 2022 Liviu Istrate, www.programming-electronics-diy.xyz (istrateliviu24@yahoo.com)
This program is free software: you can redistribute it and/or modify
it under the terms of the GNU General Public License as published by
the Free Software Foundation, either version 3 of the License, or
(at your option) any later version.
See <https://www.gnu.org/licenses/> for a copy of the GNU General Public License.
